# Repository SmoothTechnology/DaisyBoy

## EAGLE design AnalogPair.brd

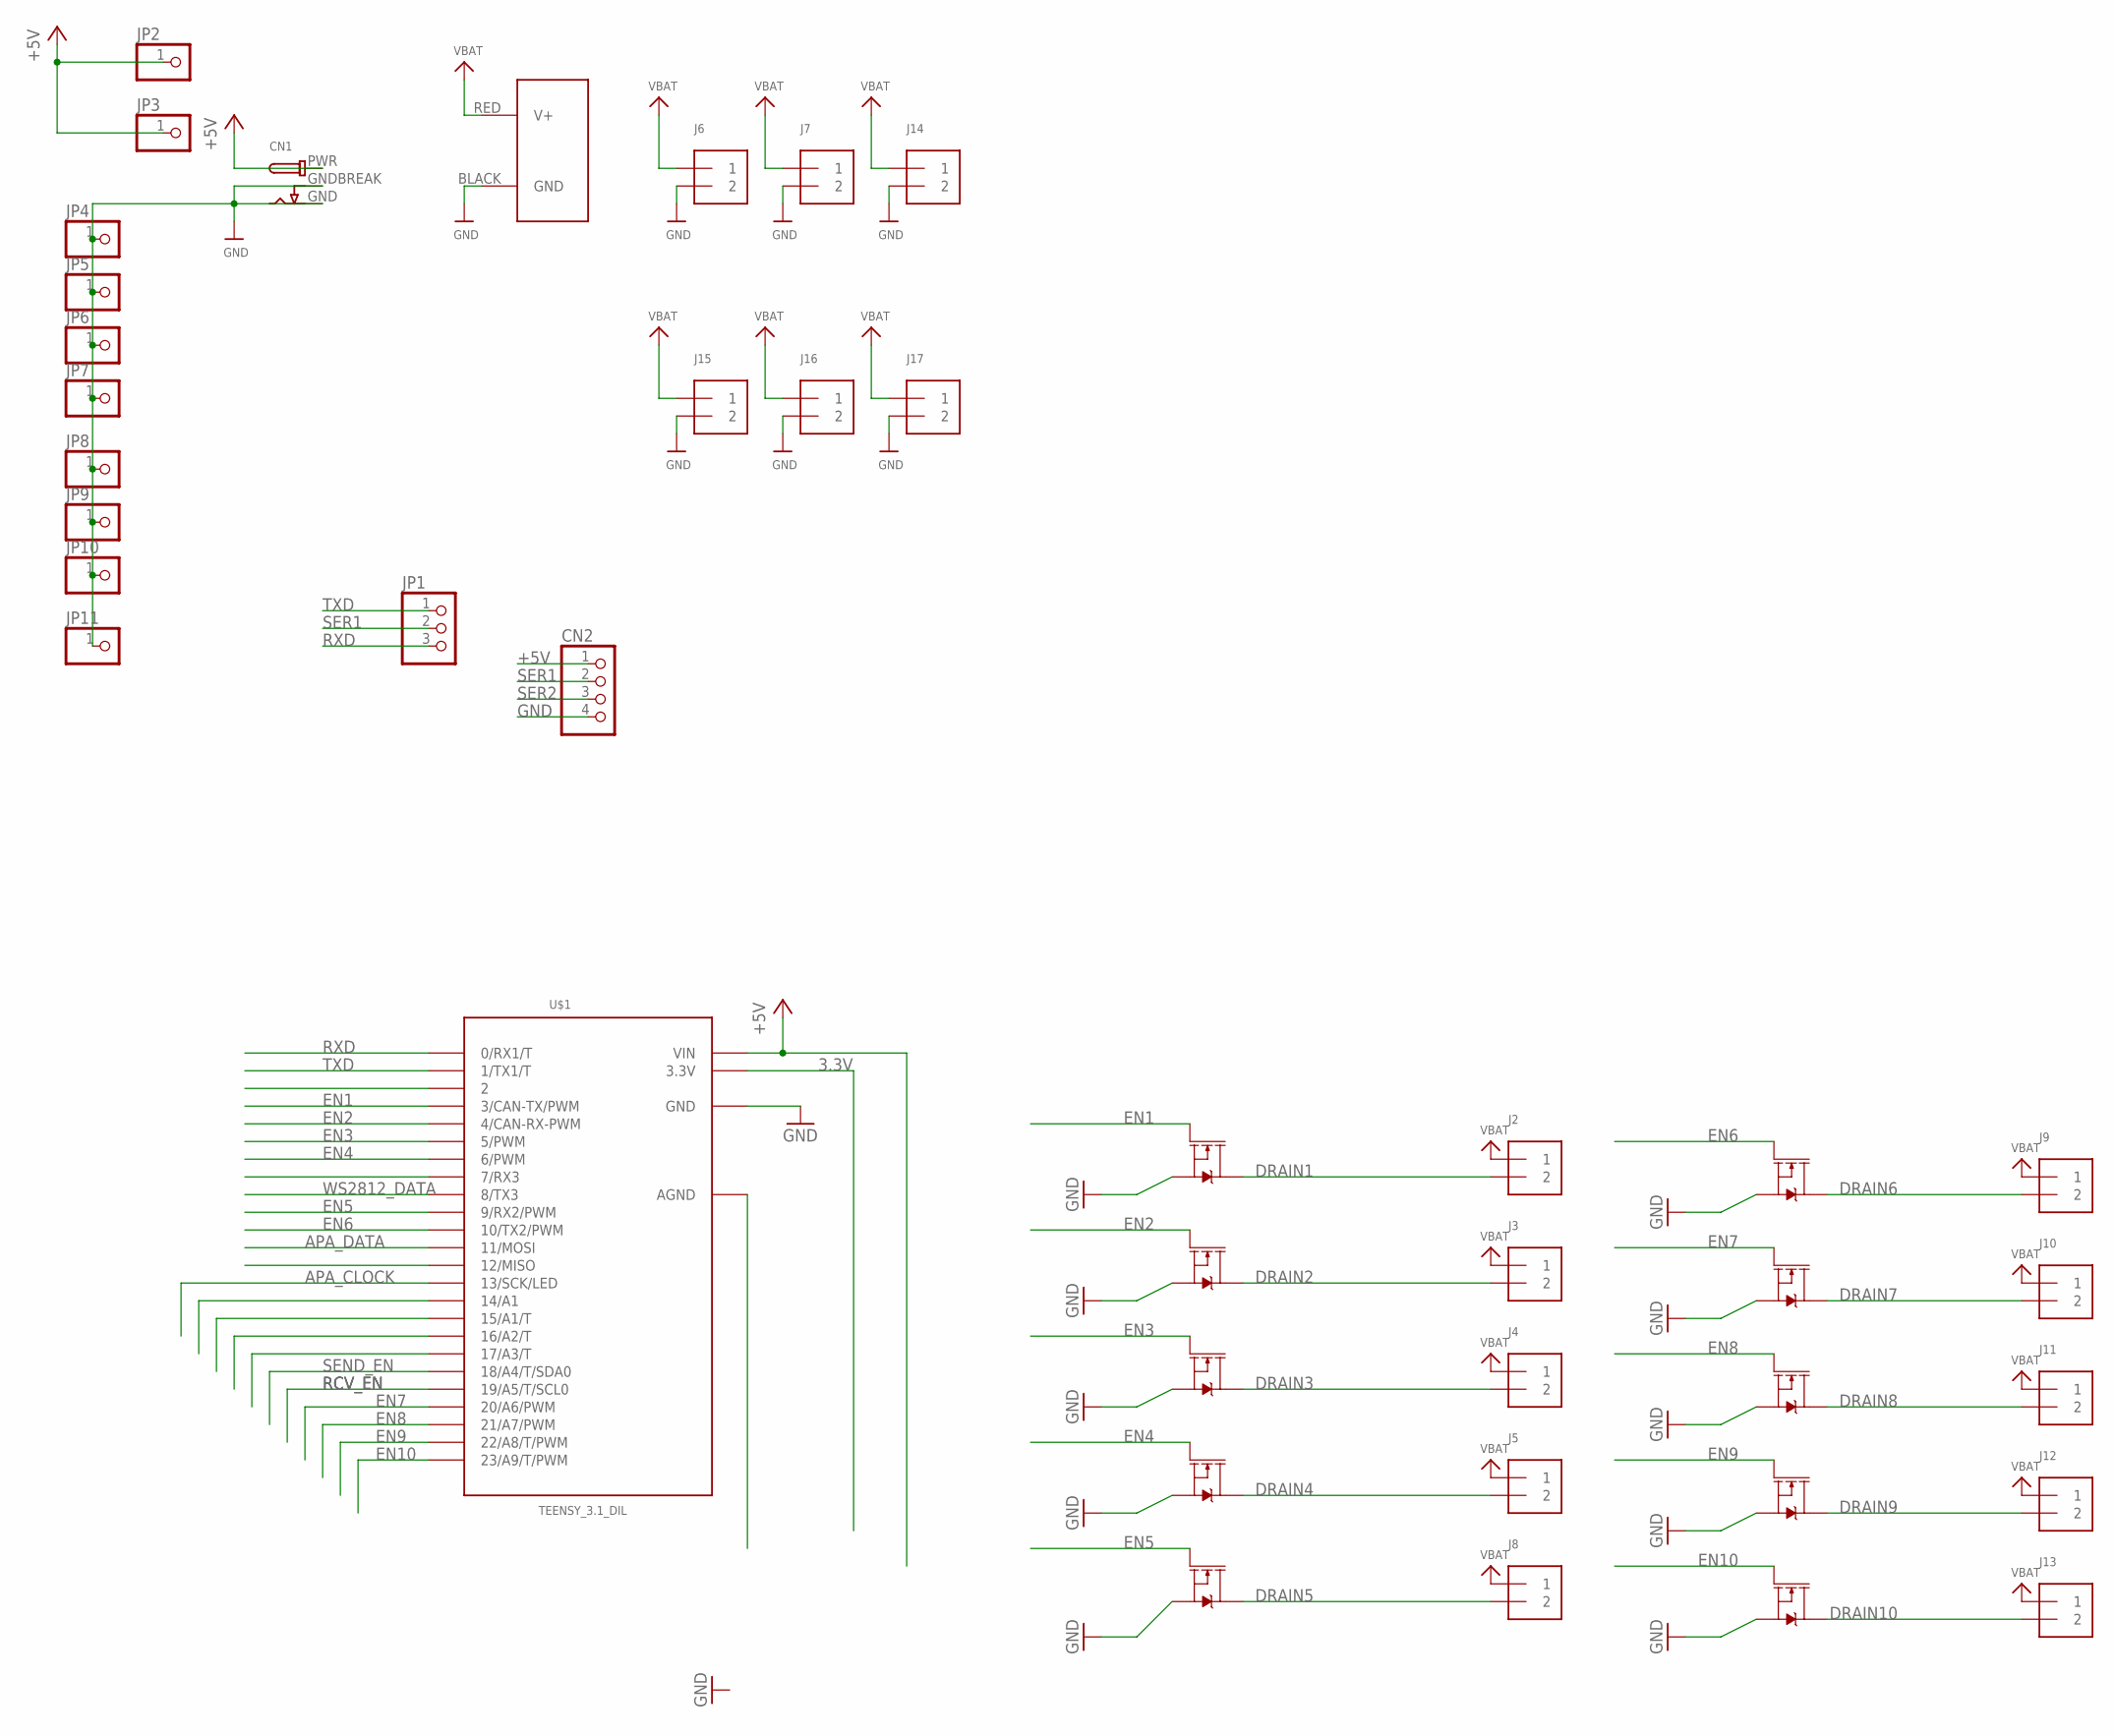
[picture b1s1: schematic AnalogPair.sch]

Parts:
CN1: DCBARRELPTH; DCJACK_2MM_PTH
CN2: HEADER-1X4; 1X04_OVAL
J1: POWERPOLE_POWER25A; POWERPOLE_PAIR_25A
J2, J3, J4, J5, J6, J7, J8, J9, J10, J11, J12, J13, J14, J15, J16, J17: TERMBLOCK_1X2; TERMBLOCK_1X2-3.5MM
JP1: PINHD-1X3; 1X03
JP2, JP3, JP4, JP5, JP6, JP7, JP8, JP9, JP10, JP11: PINHD-1X1; 1X01
Q1, Q2, Q3, Q4, Q5, Q6, Q7, Q8, Q9, Q10: 35A/25V/8.5mΩ; DPAK
U$1: TEENSY_3.1_DIL; TEENSY3-DIL

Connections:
3.3V: U$1.3.3V
+5V: CN1.PWR, CN2.1, JP2.1, JP3.1, U$1.VIN
APA_CLOCK: U$1.13 (13/SCK/LED)
APA_DATA: U$1.11 (11/MOSI)
DRAIN1: J2.2, Q1.4 (D)
DRAIN2: J3.2, Q3.4 (D)
DRAIN3: J4.2, Q5.4 (D)
DRAIN4: J5.2, Q6.4 (D)
DRAIN5: J8.2, Q2.4 (D)
DRAIN6: J9.2, Q4.4 (D)
DRAIN7: J10.2, Q7.4 (D)
DRAIN8: J11.2, Q8.4 (D)
DRAIN9: J12.2, Q9.4 (D)
DRAIN10: J13.2, Q10.4 (D)
EN1: Q1.1 (G), U$1.3 (3/CAN-TX/PWM)
EN2: Q3.1 (G), U$1.4 (4/CAN-RX-PWM)
EN3: Q5.1 (G), U$1.5 (5/PWM)
EN4: Q6.1 (G), U$1.6 (6/PWM)
EN5: Q2.1 (G), U$1.9 (9/RX2/PWM)
EN6: Q4.1 (G), U$1.10 (10/TX2/PWM)
EN7: Q7.1 (G), U$1.20/A6 (20/A6/PWM)
EN8: Q8.1 (G), U$1.21/A7 (21/A7/PWM)
EN9: Q9.1 (G), U$1.22/A8 (22/A8/T/PWM)
EN10: Q10.1 (G), U$1.23/A9 (23/A9/T/PWM)
GND: CN1.GND, CN1.GNDBREAK, CN2.4, J1.BLACK (GND), J6.2, J7.2, J14.2, J15.2, J16.2, J17.2, JP4.1, JP5.1, JP6.1, JP7.1, JP8.1, JP9.1, JP10.1, JP11.1, Q1.3 (S), Q2.3 (S), Q3.3 (S), Q4.3 (S), Q5.3 (S), Q6.3 (S), Q7.3 (S), Q8.3 (S), Q9.3 (S), Q10.3 (S), U$1.GND
RCV_EN: U$1.19/A5 (19/A5/T/SCL0)
RXD: JP1.3, U$1.0 (0/RX1/T)
SEND_EN: U$1.18/A4 (18/A4/T/SDA0)
SER1: CN2.2, JP1.2
SER2: CN2.3
TXD: JP1.1, U$1.1 (1/TX1/T)
VBAT: J1.RED (V+), J2.1, J3.1, J4.1, J5.1, J6.1, J7.1, J8.1, J9.1, J10.1, J11.1, J12.1, J13.1, J14.1, J15.1, J16.1, J17.1
WS2812_DATA: U$1.8 (8/TX3)

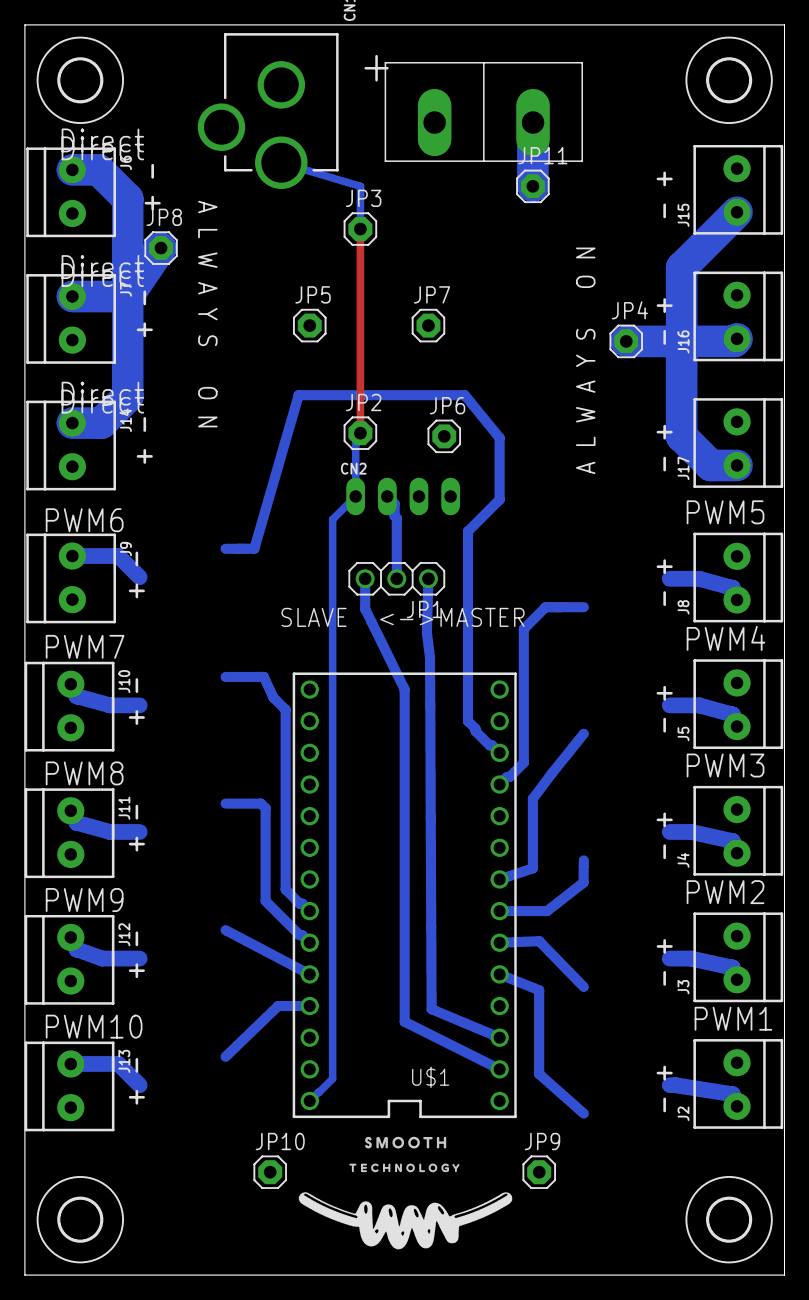
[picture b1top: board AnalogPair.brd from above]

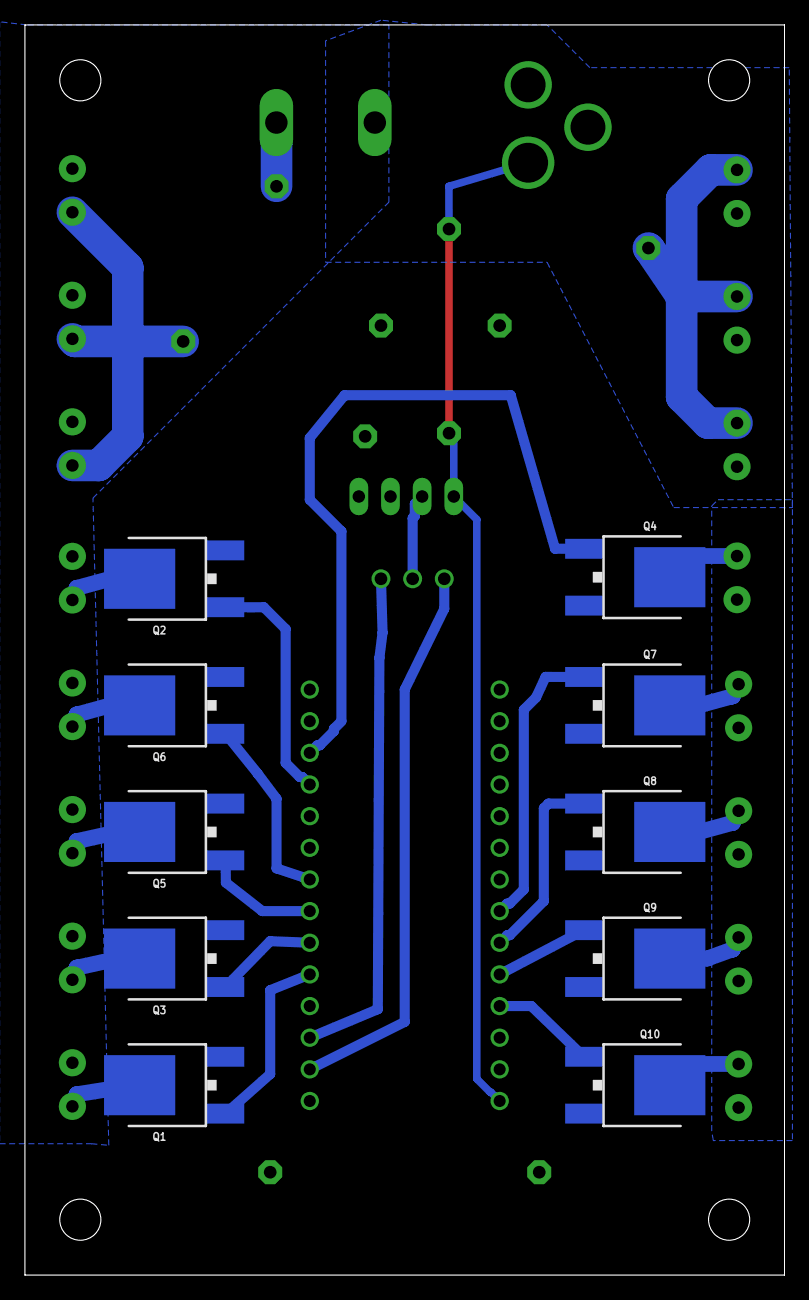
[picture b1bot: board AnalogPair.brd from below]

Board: 2 copper layers, 61.0 x 100.3 mm, 48 parts (10 on the bottom side), 26 nets.

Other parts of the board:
U$11, U$15, U$16, U$19: 3,3
U$13: SMOOTH_
U$14: TECHNOLOGY_
U$17: SMOOTH_LOGO

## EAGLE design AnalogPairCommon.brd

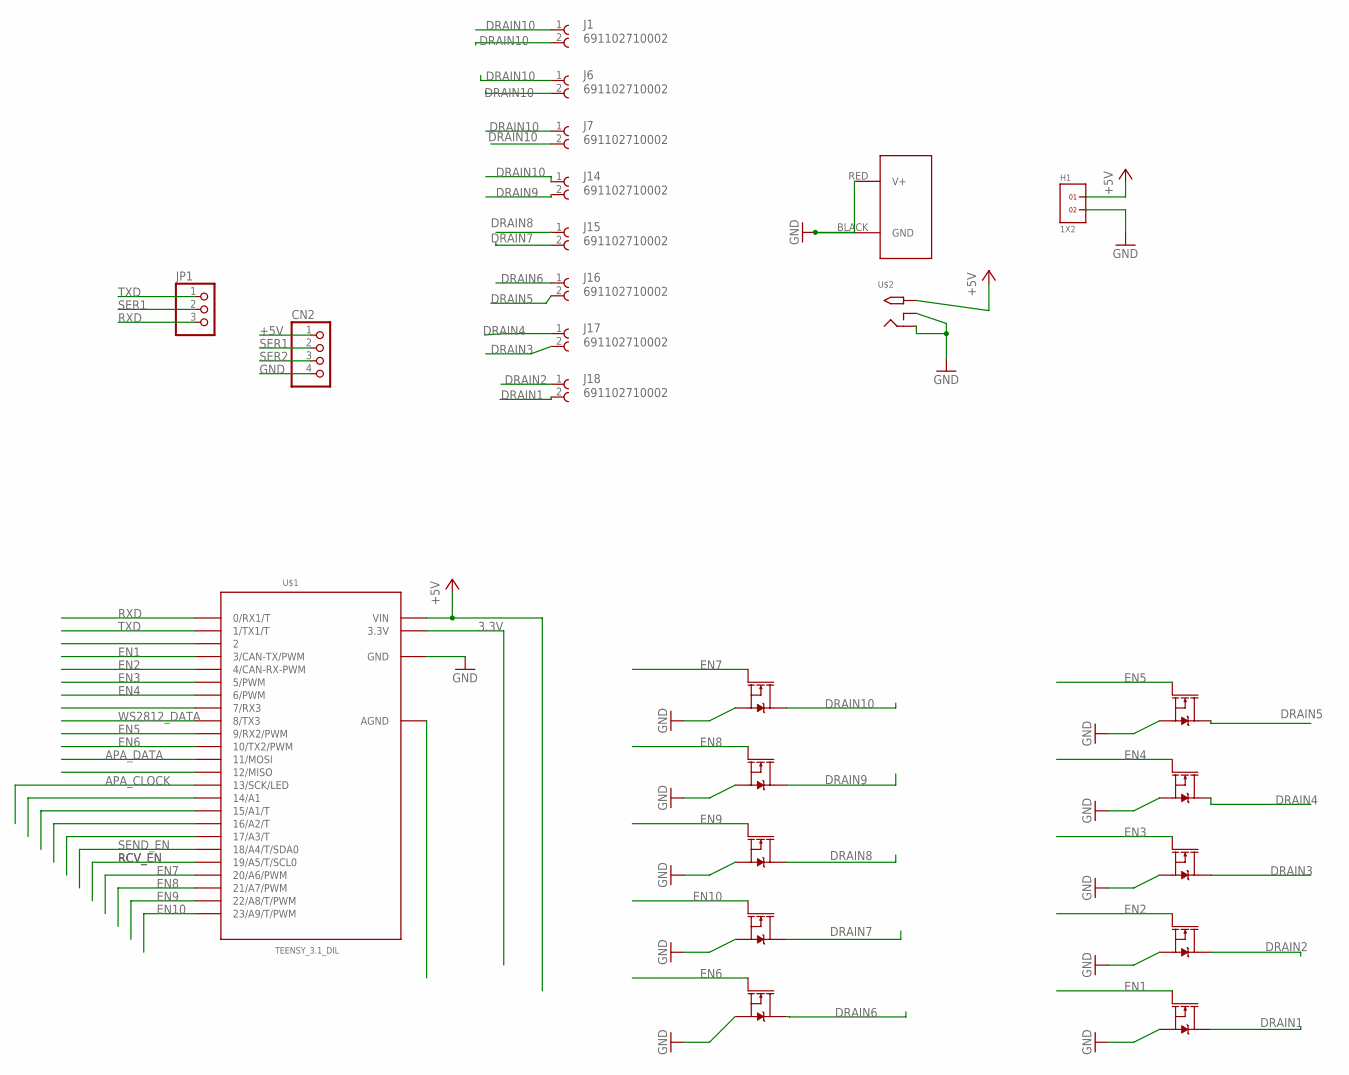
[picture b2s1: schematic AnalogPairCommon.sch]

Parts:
CN2: HEADER-1X4; 1X04_OVAL
H1: 1X2
J1, J6, J7, J14, J15, J16, J17, J18: 691102710002
J2: POWERPOLE_POWER25A; POWERPOLE_PAIR_25A
JP1: PINHD-1X3; 1X03
Q1, Q2, Q3, Q4, Q5, Q6, Q7, Q8, Q9, Q10: 35A/25V/8.5mΩ; DPAK
U$1: TEENSY_3.1_DIL; TEENSY3-DIL
U$2: 2.1MMJACKTHM; PJ-102A

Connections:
3.3V: U$1.3.3V
+5V: CN2.1, H1.1, U$1.VIN, U$2.TIP
APA_CLOCK: U$1.13 (13/SCK/LED)
APA_DATA: U$1.11 (11/MOSI)
DRAIN1: J18.2, Q10.4 (D)
DRAIN2: J18.1, Q9.4 (D)
DRAIN3: J17.2, Q8.4 (D)
DRAIN4: J17.1, Q7.4 (D)
DRAIN5: J16.2, Q4.4 (D)
DRAIN6: J16.1, Q2.4 (D)
DRAIN7: J15.2, Q6.4 (D)
DRAIN8: J15.1, Q5.4 (D)
DRAIN9: J14.2, Q3.4 (D)
DRAIN10: J1.1, J1.2, J6.1, J6.2, J7.1, J7.2, J14.1, Q1.4 (D)
EN1: Q10.1 (G), U$1.3 (3/CAN-TX/PWM)
EN2: Q9.1 (G), U$1.4 (4/CAN-RX-PWM)
EN3: Q8.1 (G), U$1.5 (5/PWM)
EN4: Q7.1 (G), U$1.6 (6/PWM)
EN5: Q4.1 (G), U$1.9 (9/RX2/PWM)
EN6: Q2.1 (G), U$1.10 (10/TX2/PWM)
EN7: Q1.1 (G), U$1.20/A6 (20/A6/PWM)
EN8: Q3.1 (G), U$1.21/A7 (21/A7/PWM)
EN9: Q5.1 (G), U$1.22/A8 (22/A8/T/PWM)
EN10: Q6.1 (G), U$1.23/A9 (23/A9/T/PWM)
GND: CN2.4, H1.2, J2.BLACK (GND), J2.RED (V+), Q1.3 (S), Q2.3 (S), Q3.3 (S), Q4.3 (S), Q5.3 (S), Q6.3 (S), Q7.3 (S), Q8.3 (S), Q9.3 (S), Q10.3 (S), U$1.GND, U$2.RING, U$2.RING_SW
RCV_EN: U$1.19/A5 (19/A5/T/SCL0)
RXD: JP1.3, U$1.0 (0/RX1/T)
SEND_EN: U$1.18/A4 (18/A4/T/SDA0)
SER1: CN2.2, JP1.2
SER2: CN2.3
TXD: JP1.1, U$1.1 (1/TX1/T)
WS2812_DATA: U$1.8 (8/TX3)

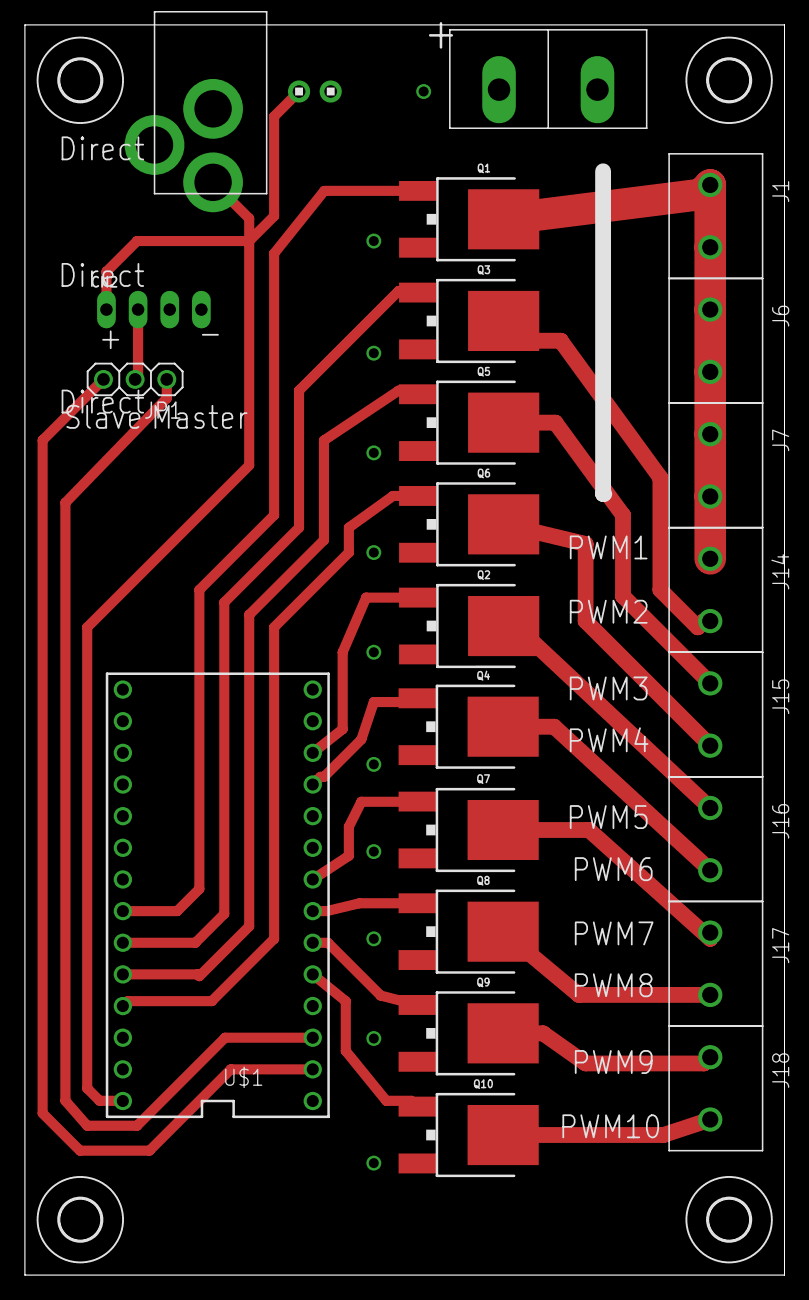
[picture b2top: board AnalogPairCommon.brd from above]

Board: 2 copper layers, 61.0 x 100.3 mm, 28 parts (0 on the bottom side), 25 nets.

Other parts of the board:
U$11, U$15, U$16, U$19: 3,3

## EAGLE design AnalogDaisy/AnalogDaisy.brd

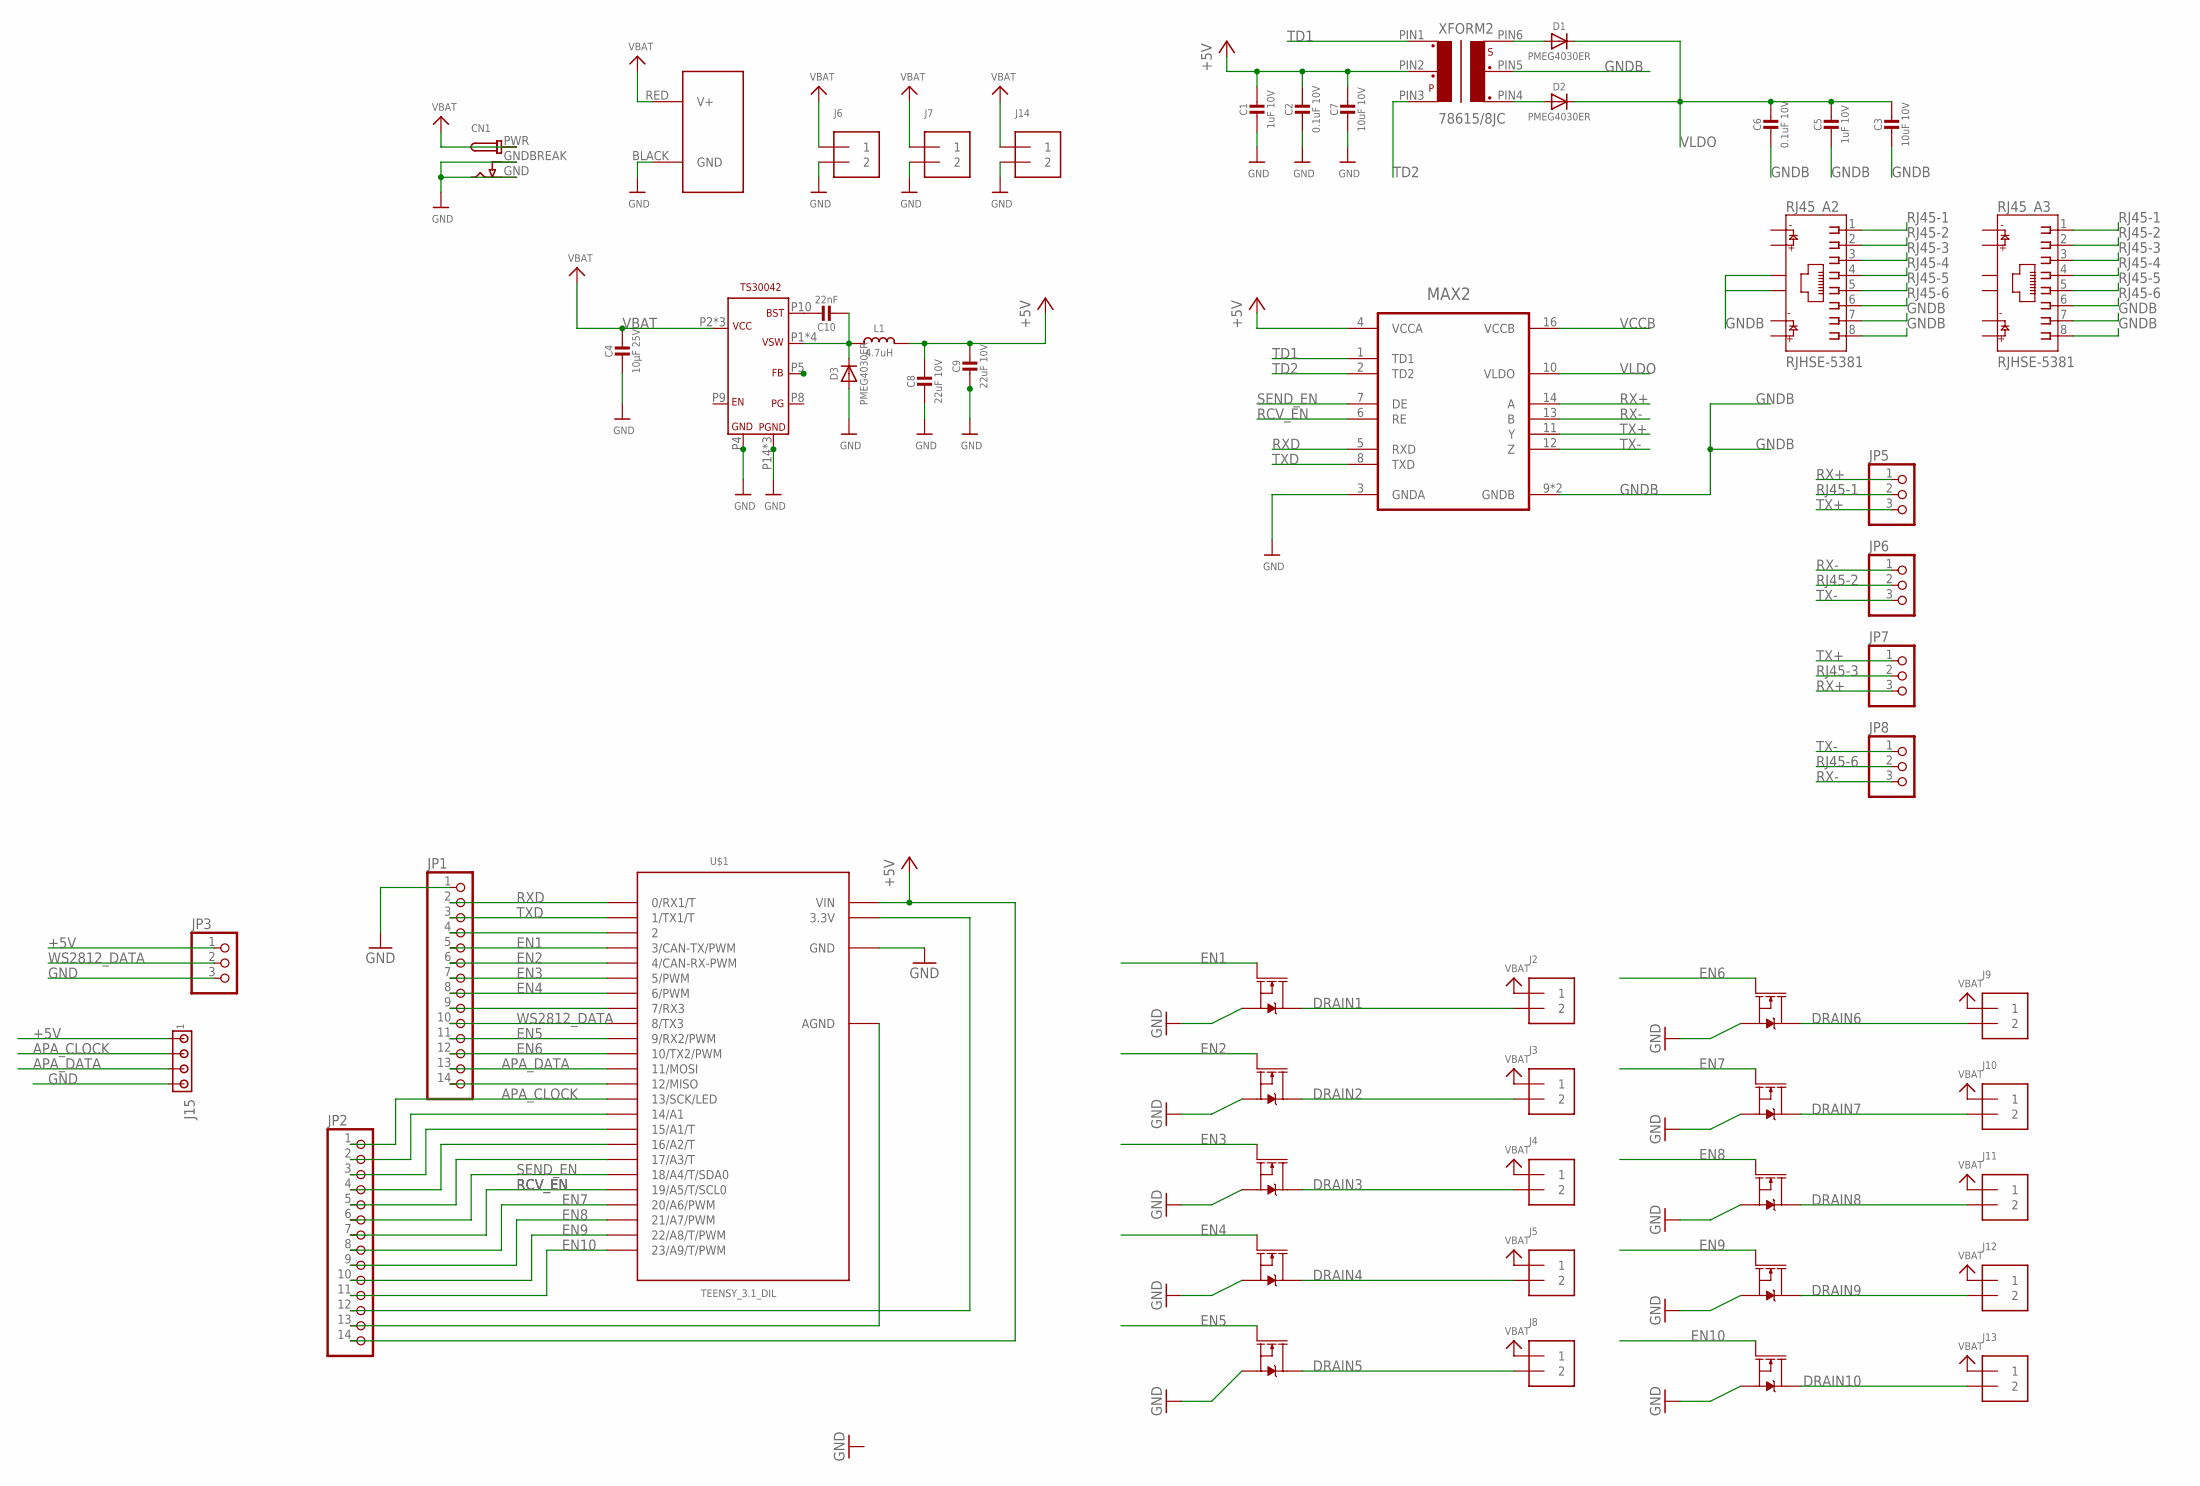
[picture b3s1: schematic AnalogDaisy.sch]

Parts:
C1, C5: 1uF 10V; 0603-MINI
C2, C6: 0.1uF 10V; 0603-MINI
C3, C7: 10uF 10V; 0603-MINI
C4: 10µF 25V; 0603-MINI
C8, C9: 22uF 10V; 0603-MINI
C10: 22nF; 0603-MINI
CN1: DCBARRELPTH; DCJACK_2MM_PTH
D1, D2, D3: PMEG4030ER; SOD-123
J1: POWERPOLE_POWER45A_DRILL; POWERPOLE_PAIR_45A_HOLE
J2, J3, J4, J5, J6, J7, J8, J9, J10, J11, J12, J13, J14: TERMBLOCK_1X2; TERMBLOCK_1X2-3.5MM
J15: 4PIN-JST/TE; BOARDMOUNT-LED
JP1, JP2: PINHD-1X14; 1X14
JP3, JP5, JP6, JP7, JP8: PINHD-1X3; 1X03
L1: 4.7uH; INDUCTOR_5X5MM_TDK_VLC5045
MAX2: MAX14853GWE+; SOIC127P1034X267-16N
Q1, Q2, Q3, Q4, Q5, Q6, Q7, Q8, Q9, Q10: 35A/25V/8.5mΩ; DPAK
RJ45_A2, RJ45_A3: RJHSE-5381; AMPHENOL_RJHSE-5381
U$1: TEENSY_3.1_DIL; TEENSY3-DIL
U$2: BUCK_CONVERTER; QFN-16
XFORM2: 78615/8JC; 0.1_SMD

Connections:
+3V1: U$2.P5 (FB)
+5V: C1.1, C2.1, C7.1, C8.1, C9.1, J15.1, JP2.14, JP3.1, L1.P$2 (2), MAX2.4 (VCCA), U$1.VIN, XFORM2.PIN2 (2)
APA_CLOCK: J15.2, JP2.1, U$1.13 (13/SCK/LED)
APA_DATA: J15.3, JP1.13, U$1.11 (11/MOSI)
DRAIN1: J2.2, Q1.4 (D)
DRAIN2: J3.2, Q3.4 (D)
DRAIN3: J4.2, Q5.4 (D)
DRAIN4: J5.2, Q6.4 (D)
DRAIN5: J8.2, Q2.4 (D)
DRAIN6: J9.2, Q4.4 (D)
DRAIN7: J10.2, Q7.4 (D)
DRAIN8: J11.2, Q8.4 (D)
DRAIN9: J12.2, Q9.4 (D)
DRAIN10: J13.2, Q10.4 (D)
EN1: JP1.5, Q1.1 (G), U$1.3 (3/CAN-TX/PWM)
EN2: JP1.6, Q3.1 (G), U$1.4 (4/CAN-RX-PWM)
EN3: JP1.7, Q5.1 (G), U$1.5 (5/PWM)
EN4: JP1.8, Q6.1 (G), U$1.6 (6/PWM)
EN5: JP1.11, Q2.1 (G), U$1.9 (9/RX2/PWM)
EN6: JP1.12, Q4.1 (G), U$1.10 (10/TX2/PWM)
EN7: JP2.8, Q7.1 (G), U$1.20/A6 (20/A6/PWM)
EN8: JP2.9, Q8.1 (G), U$1.21/A7 (21/A7/PWM)
EN9: JP2.10, Q9.1 (G), U$1.22/A8 (22/A8/T/PWM)
EN10: JP2.11, Q10.1 (G), U$1.23/A9 (23/A9/T/PWM)
GND: C1.2, C2.2, C4.2, C7.2, C8.2, C9.2, CN1.GND, CN1.GNDBREAK, D3.A, J1.BLACK (GND), J6.2, J7.2, J14.2, J15.4, JP1.1, JP3.3, MAX2.3 (GNDA), Q1.3 (S), Q2.3 (S), Q3.3 (S), Q4.3 (S), Q5.3 (S), Q6.3 (S), Q7.3 (S), Q8.3 (S), Q9.3 (S), Q10.3 (S), U$1.GND, U$2.P4 (GND), U$2.P14 (PGND), U$2.P15 (PGND), U$2.PAD (PGND)
GNDB: C3.2, C5.2, C6.2, MAX2.9 (GNDB), MAX2.15 (GNDB), RJ45_A2.7, RJ45_A2.8, RJ45_A2.S1, RJ45_A2.S2, RJ45_A3.7, RJ45_A3.8, XFORM2.PIN5 (5)
unnamed: C10.1, U$2.P10 (BST)
unnamed: D1.A, XFORM2.PIN6 (6)
unnamed: JP2.12, U$1.3.3V
unnamed: C10.2, D3.C, L1.P$1 (1), U$2.P1 (VSW), U$2.P12 (VSW), U$2.P13 (VSW), U$2.P16 (VSW)
unnamed: D2.A, XFORM2.PIN4 (4)
unnamed: JP1.4, U$1.2
unnamed: JP1.9, U$1.7 (7/RX3)
unnamed: JP1.14, U$1.12 (12/MISO)
unnamed: JP2.2, U$1.14/A0 (14/A1)
unnamed: JP2.3, U$1.15/A1 (15/A1/T)
unnamed: JP2.4, U$1.16/A2 (16/A2/T)
unnamed: JP2.5, U$1.17/A3 (17/A3/T)
unnamed: JP2.13, U$1.AGND
RCV_EN: JP2.7, MAX2.6 (RE), U$1.19/A5 (19/A5/T/SCL0)
RJ45-1: JP5.2, RJ45_A2.1, RJ45_A3.1
RJ45-2: JP6.2, RJ45_A2.2, RJ45_A3.2
RJ45-3: JP7.2, RJ45_A2.3, RJ45_A3.3
RJ45-4: RJ45_A2.4, RJ45_A3.4
RJ45-5: RJ45_A2.5, RJ45_A3.5
RJ45-6: JP8.2, RJ45_A2.6, RJ45_A3.6
RX+: JP5.1, JP7.3, MAX2.14 (A)
RX-: JP6.1, JP8.3, MAX2.13 (B)
RXD: JP1.2, MAX2.5 (RXD), U$1.0 (0/RX1/T)
SEND_EN: JP2.6, MAX2.7 (DE), U$1.18/A4 (18/A4/T/SDA0)
TD1: MAX2.1 (TD1), XFORM2.PIN1 (1)
TD2: MAX2.2 (TD2), XFORM2.PIN3 (3)
TX+: JP5.3, JP7.1, MAX2.11 (Y)
TX-: JP6.3, JP8.1, MAX2.12 (Z)
TXD: JP1.3, MAX2.8 (TXD), U$1.1 (1/TX1/T)
VBAT: C4.1, CN1.PWR, J1.RED (V+), J2.1, J3.1, J4.1, J5.1, J8.1, J9.1, J10.1, J11.1, J12.1, J13.1, U$2.P2 (VCC), U$2.P3 (VCC), U$2.P11 (VCC)
VCCB: MAX2.16 (VCCB)
VLDO: C3.1, C5.1, C6.1, D1.C, D2.C, MAX2.10 (VLDO)
WS2812_DATA: JP1.10, JP3.2, U$1.8 (8/TX3)

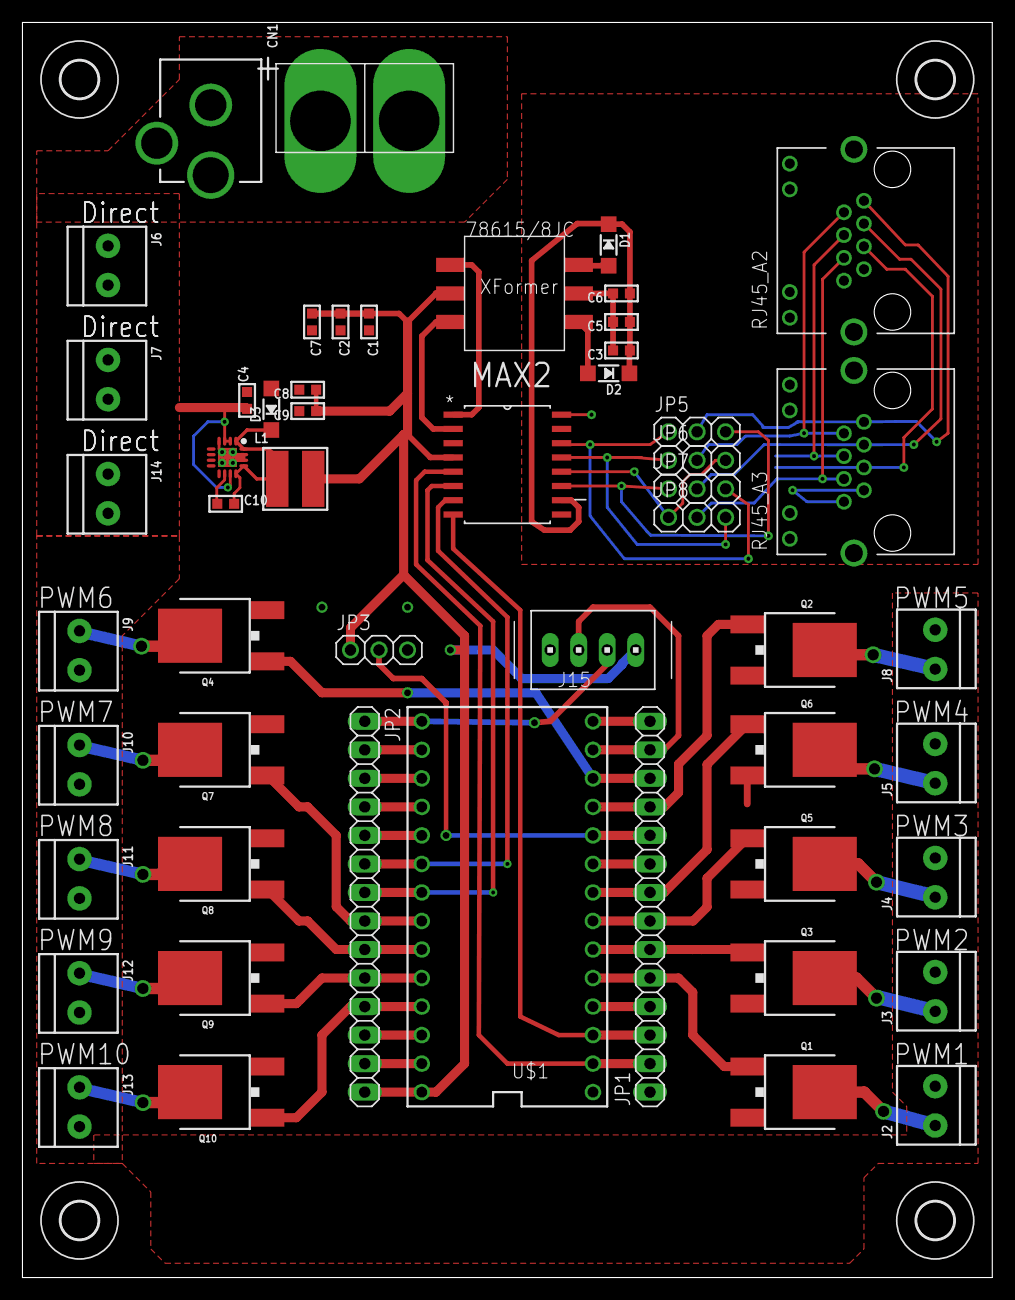
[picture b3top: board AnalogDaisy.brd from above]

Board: 2 copper layers, 86.4 x 111.8 mm, 57 parts (0 on the bottom side), 57 nets.

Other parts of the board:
U$11, U$15, U$16, U$19: 3,3

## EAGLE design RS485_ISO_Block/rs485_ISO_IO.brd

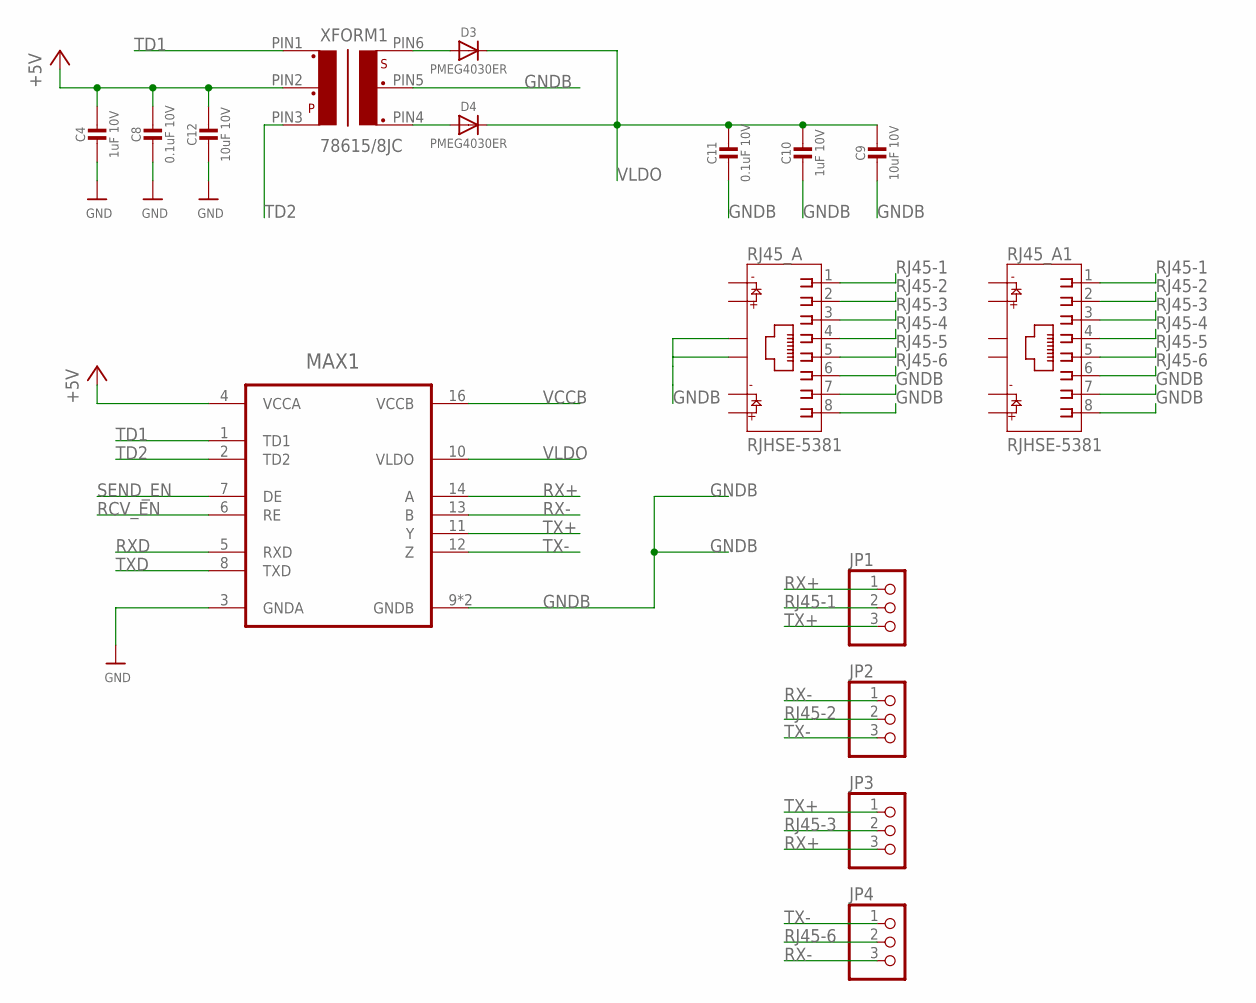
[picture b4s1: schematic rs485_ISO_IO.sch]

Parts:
C4, C10: 1uF 10V; 0603-MINI
C8, C11: 0.1uF 10V; 0603-MINI
C9, C12: 10uF 10V; 0603-MINI
D3, D4: PMEG4030ER; SOD-123
JP1, JP2, JP3, JP4: PINHD-1X3; 1X03
MAX1: MAX14853GWE+; SOIC127P1034X267-16N
RJ45_A, RJ45_A1: RJHSE-5381; AMPHENOL_RJHSE-5381
XFORM1: 78615/8JC; 0.1_SMD

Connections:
+5V: C4.1, C8.1, C12.1, MAX1.4 (VCCA), XFORM1.PIN2 (2)
GND: C4.2, C8.2, C12.2, MAX1.3 (GNDA)
GNDB: C9.2, C10.2, C11.2, MAX1.9 (GNDB), MAX1.15 (GNDB), RJ45_A.7, RJ45_A.8, RJ45_A.S1, RJ45_A.S2, RJ45_A1.7, RJ45_A1.8, XFORM1.PIN5 (5)
unnamed: D3.A, XFORM1.PIN6 (6)
unnamed: D4.A, XFORM1.PIN4 (4)
RCV_EN: MAX1.6 (RE)
RJ45-1: JP1.2, RJ45_A.1, RJ45_A1.1
RJ45-2: JP2.2, RJ45_A.2, RJ45_A1.2
RJ45-3: JP3.2, RJ45_A.3, RJ45_A1.3
RJ45-4: RJ45_A.4, RJ45_A1.4
RJ45-5: RJ45_A.5, RJ45_A1.5
RJ45-6: JP4.2, RJ45_A.6, RJ45_A1.6
RX+: JP1.1, JP3.3, MAX1.14 (A)
RX-: JP2.1, JP4.3, MAX1.13 (B)
RXD: MAX1.5 (RXD)
SEND_EN: MAX1.7 (DE)
TD1: MAX1.1 (TD1), XFORM1.PIN1 (1)
TD2: MAX1.2 (TD2), XFORM1.PIN3 (3)
TX+: JP1.3, JP3.1, MAX1.11 (Y)
TX-: JP2.3, JP4.1, MAX1.12 (Z)
TXD: MAX1.8 (TXD)
VCCB: MAX1.16 (VCCB)
VLDO: C9.1, C10.1, C11.1, D3.C, D4.C, MAX1.10 (VLDO)

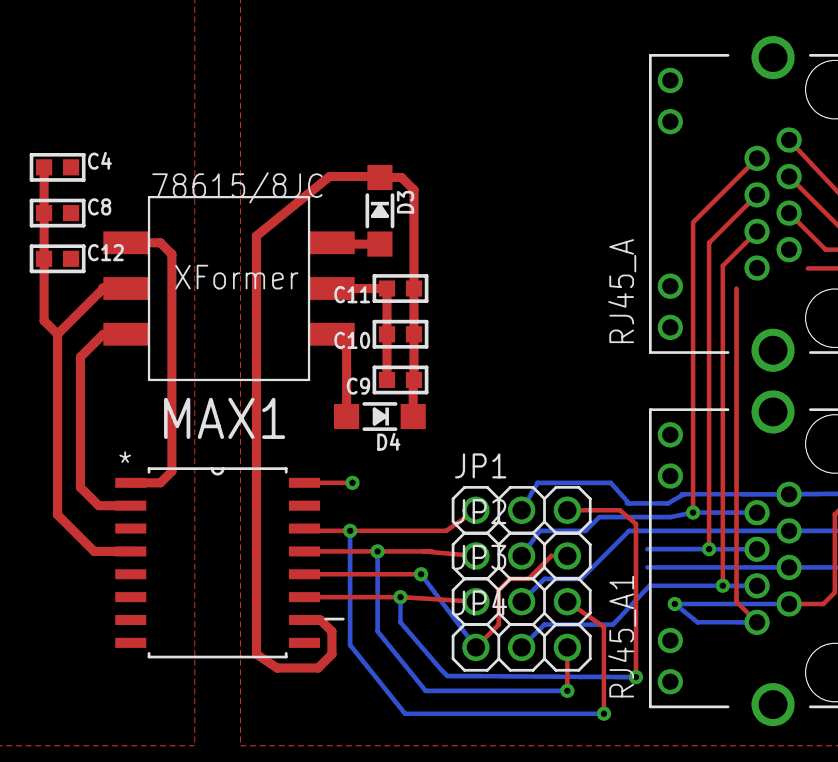
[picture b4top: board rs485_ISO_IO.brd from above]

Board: 2 copper layers, 16 parts (0 on the bottom side), 18 nets.

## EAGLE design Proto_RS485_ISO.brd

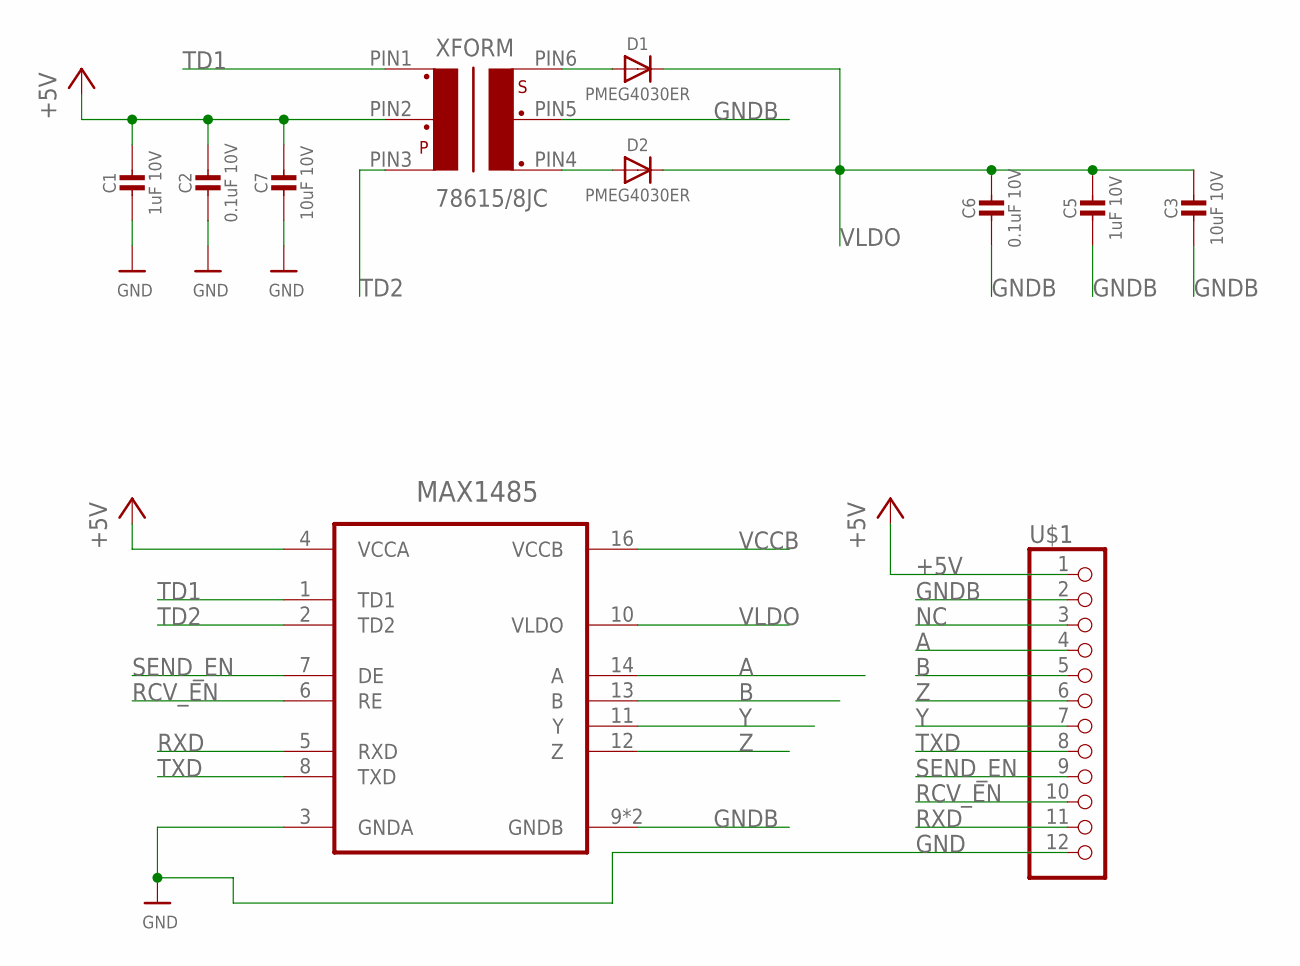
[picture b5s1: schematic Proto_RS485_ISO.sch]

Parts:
C1, C5: 1uF 10V; 0603-MINI
C2, C6: 0.1uF 10V; 0603-MINI
C3, C7: 10uF 10V; 0603-MINI
D1, D2: PMEG4030ER; SOD-123
MAX1485: MAX14853GWE+; SOIC127P1034X267-16N
U$1: PINHD-1X12; 1X12
XFORM: 78615/8JC; 0.1_SMD

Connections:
+5V: C1.1, C2.1, C7.1, MAX1485.4 (VCCA), U$1.1, XFORM.PIN2 (2)
A: MAX1485.14 (A), U$1.4
B: MAX1485.13 (B), U$1.5
GND: C1.2, C2.2, C7.2, MAX1485.3 (GNDA), U$1.12
GNDB: C3.2, C5.2, C6.2, MAX1485.9 (GNDB), MAX1485.15 (GNDB), U$1.2, XFORM.PIN5 (5)
unnamed: D1.A, XFORM.PIN6 (6)
unnamed: D2.A, XFORM.PIN4 (4)
NC: U$1.3
RCV_EN: MAX1485.6 (RE), U$1.10
RXD: MAX1485.5 (RXD), U$1.11
SEND_EN: MAX1485.7 (DE), U$1.9
TD1: MAX1485.1 (TD1), XFORM.PIN1 (1)
TD2: MAX1485.2 (TD2), XFORM.PIN3 (3)
TXD: MAX1485.8 (TXD), U$1.8
VCCB: MAX1485.16 (VCCB)
VLDO: C3.1, C5.1, C6.1, D1.C, D2.C, MAX1485.10 (VLDO)
Y: MAX1485.11 (Y), U$1.7
Z: MAX1485.12 (Z), U$1.6

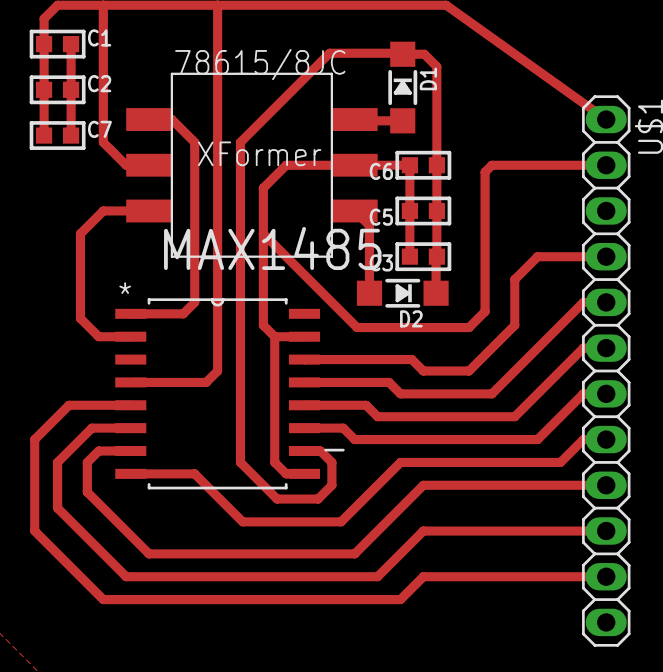
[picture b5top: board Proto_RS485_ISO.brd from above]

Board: 2 copper layers, 11 parts (0 on the bottom side), 16 nets.

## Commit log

2018-01-25 initial commit with othermill designed pwm board
2018-01-25 ignore eagle backup files
2018-01-25 added analogdaisy
2018-01-25 moved inductor, git test
2018-01-25 added proto board
2018-01-28 Added iso I/O Block
2018-01-29 Updated AnalogDaisy
2018-01-29 Updated AnalogDaisy Wiring
2018-01-30 Updated AnalogPair
2018-01-31 Updated AnalogPairCommon
2018-01-31 MOved silk screen into place
2018-01-31 Fixed silk
2018-01-31 added silks and submitted analogpair to allpcb.com

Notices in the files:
parts and their libraries:
microbuilder: This work is placed in the public domain, and may be freely used for commercial and non-commercial work with the following conditions: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
SparkFun-DiscreteSemi: Licensing: Creative Commons ShareAlike 4.0 International - https://creativecommons.org/licenses/by-sa/4.0
